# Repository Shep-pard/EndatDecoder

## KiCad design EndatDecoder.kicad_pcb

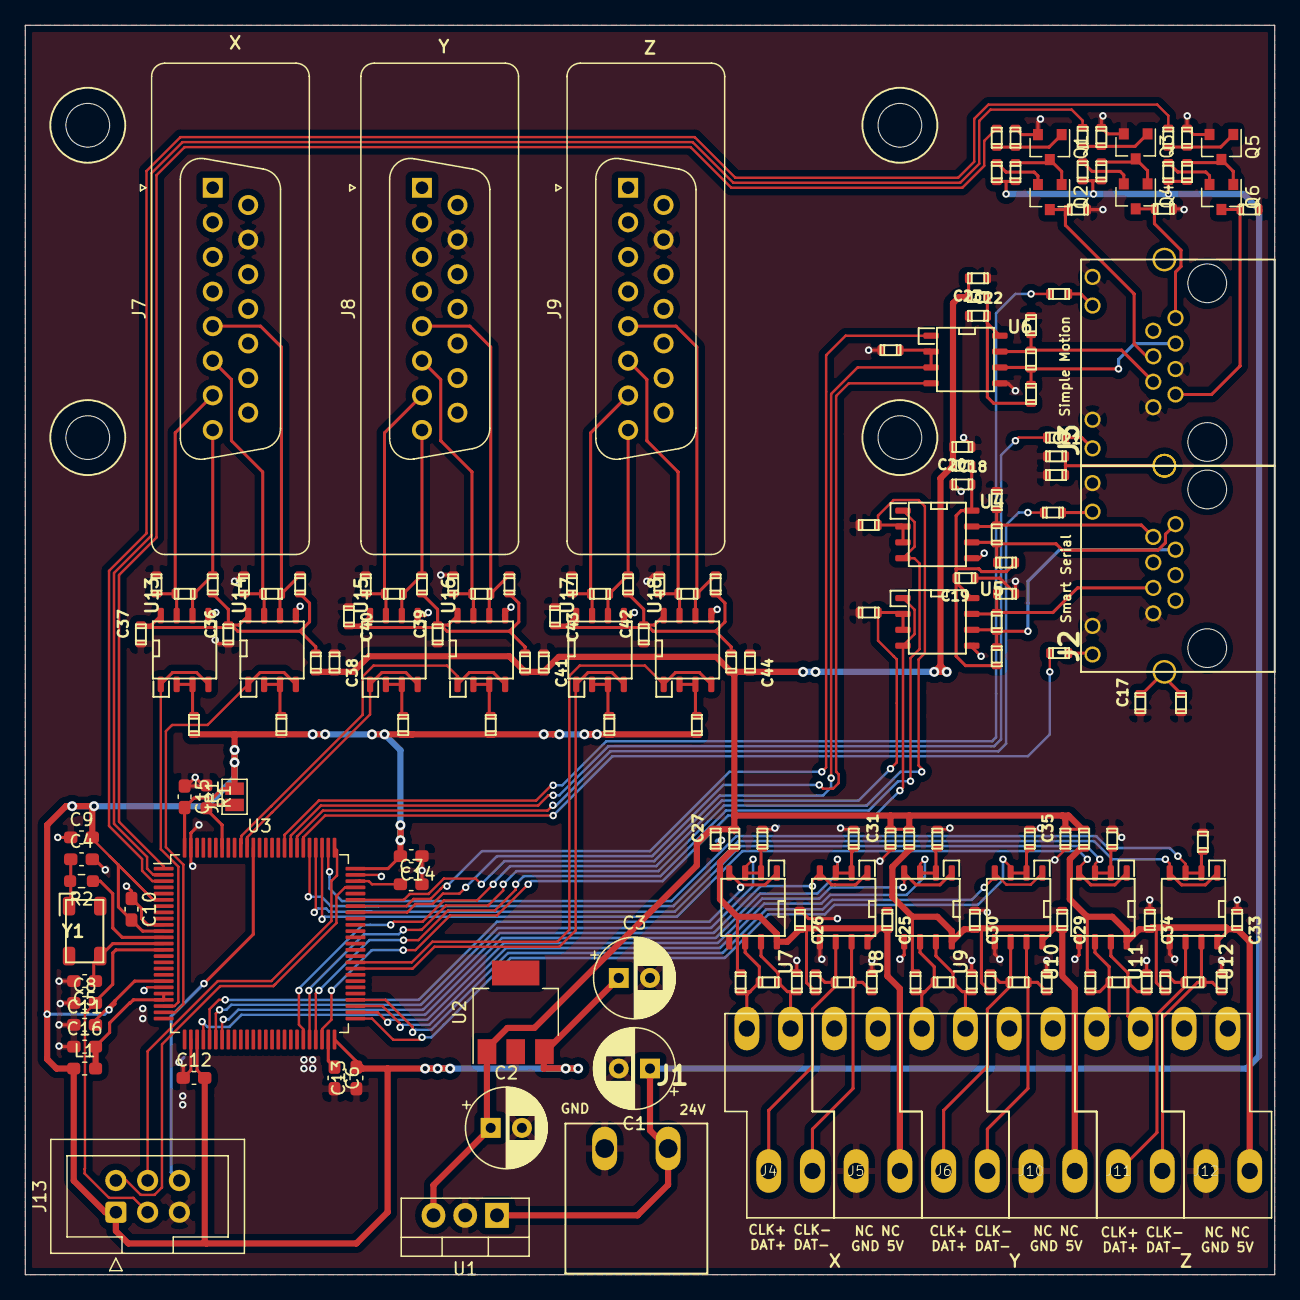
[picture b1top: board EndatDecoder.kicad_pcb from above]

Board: 2 copper layers, 100.0 x 100.0 mm, 176 parts (0 on the bottom side), 108 nets.

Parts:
C1, C2, C3: CP; CP_Radial_D6.3mm_P2.50mm
C4, C5: 18p; C_0603_1608Metric_Pad1.08x0.95mm_HandSolder
C6, C7: 2.2u; C_0603_1608Metric_Pad1.08x0.95mm_HandSolder
C8, C9, C10, C11, C12, C13, C14, C15, C16: 100n; C_0603_1608Metric_Pad1.08x0.95mm_HandSolder
C17, C18, C19, C20, C21, C22, C23, C25, C26, C27, C29, C30, C31, C33, C34, C35, C36, C37, C38, C39, C40, C41, C42, C43, C44: 100n; C_0603
J1: Conn_01x02; RM5.08_1x2
J2, J3: RJ45_LED
J4, J5, J6, J10, J11, J12: Conn_01x04; TERMINAL_BLOCK_2PIN_3.5
J7, J8, J9: DB15_Female; DSUB-15_Female_Vertical_P2.77x2.84mm
J13: Conn_02x03_Odd_Even; IDC-Header_2x03_P2.54mm_Vertical
JP1: Jumper_2_Open; SolderJumper-2_P1.3mm_Open_Pad1.0x1.5mm
L1: 220r 700mA; L_0603_1608Metric_Pad1.05x0.95mm_HandSolder
L2, L3, L4, L5, L6, L7, L8, L9: 220r 700mA; R_0603
Q1, Q3, Q5: AO3400A; SOT-23
Q2, Q4, Q6: AO3401A; SOT-23
R1: R; R_0603_1608Metric_Pad0.98x0.95mm_HandSolder
R2: 0; R_0603_1608Metric_Pad0.98x0.95mm_HandSolder
R3, R12, R32, R33, R34, R43: 120; R_0603
R4, R6, R7, R9, R10, R11, R14, R15, R16, R18, R20, R22, R23, R24, R26, R28, R29, R31, R35, R37, R38, R40, R46, R48, R49, R51, R57, R59, R60, R62, R65, R67, R68, R70, R71, R72, R73, R75, R76, R78, R79, R80, R81, R83, R84, R86, R87, R88: 10k; R_0603
R5, R8, R17, R36, R39, R41, R42, R47, R50, R52, R53, R58, R61, R63, R64, R66, R69, R74, R77, R82, R85: 1k; R_0603
R13, R19, R21, R25, R27, R30: 100; R_0603
U1: LM7805_TO220; TO-220-3_Vertical
U2: L78033; SOT-223
U3: STM32F405VGTx; LQFP-100_14x14mm_P0.5mm
U4, U5, U6, U7, U8, U9, U10, U11, U12, U13, U14, U15, U16, U17, U18: SN65176B; SOIC-8-N
U19, U20, U21, U22: non_plated; non_plated_3mm
Y1: Crystal; Crystal_SMD_0503_4Pads

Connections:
+3.3VA: C16.2, L1.2, U3.21, U3.22
+3V3: C3.1, C9.2, C10.2, C11.2, C12.2, C13.2, C14.2, C15.2, J13.1, JP1.2, L1.1, R71.1, R72.1, R79.1, R80.1, R87.1, R88.1, U2.3, U3.6, U3.11, U3.19, U3.28, U3.50, U3.75, U3.100
+5F: C2.1, C20.1, C23.1, C27.1, C31.1, C35.1, C38.1, C41.1, C44.1, L2.2, L3.2, L4.2, L5.2, L6.2, L7.2, L8.2, L9.2, U1.3, U2.1
+24V: C1.1, J1.1, R15.1, R19.1, R23.1, R25.1, R29.1, R30.1, U1.1
/Endat1/CLK: U3.30, U7.1, U7.4
/Endat1/CLK_EN: R41.1, U3.31, U7.2, U7.3
/Endat1/MOSI: U3.32, U8.1, U8.4
/Endat1/MOSI_EN: R42.1, U3.29, U8.2, U8.3
/Endat2/CLK: U3.52, U9.1, U9.4
/Endat2/CLK_EN: R52.1, U3.53, U9.2, U9.3
/Endat2/MOSI: U3.54, U10.1, U10.4
/Endat2/MOSI_EN: R53.1, U3.51, U10.2, U10.3
/Endat3/CLK: U3.78, U11.1, U11.4
/Endat3/CLK_EN: R63.1, U3.79, U11.2, U11.3
/Endat3/MOSI: U3.80, U12.1, U12.4
/Endat3/MOSI_EN: R64.1, U3.77, U12.2, U12.3
/QuadOut1/A: U3.23, U13.1, U13.4
/QuadOut1/B: U3.24, U14.1, U14.4
/QuadOut1/DIR1: R71.2, U13.2, U13.3
/QuadOut1/DIR2: R72.2, U14.2, U14.3
/QuadOut2/A: U3.90, U15.1, U15.4
/QuadOut2/B: U3.91, U16.1, U16.4
/QuadOut2/DIR1: R79.2, U15.2, U15.3
/QuadOut2/DIR2: R80.2, U16.2, U16.3
/QuadOut3/A: U3.59, U17.1, U17.4
/QuadOut3/B: U3.60, U18.1, U18.4
/QuadOut3/DIR1: R87.2, U17.2, U17.3
/QuadOut3/DIR2: R88.2, U18.2, U18.3
/SimpleMotionV2/DIR: R24.1, U3.70, U6.2, U6.3
/SimpleMotionV2/EN: R27.2, U3.3
/SimpleMotionV2/EN_24: J3.7, Q6.3, R31.1
/SimpleMotionV2/LD1: R34.2, U3.84
/SimpleMotionV2/LD2: R43.2, U3.83
/SimpleMotionV2/RX: U3.69, U6.1
/SimpleMotionV2/STO1: R13.2, U3.1
/SimpleMotionV2/STO1_24: J3.4, Q2.3, R20.1
/SimpleMotionV2/STO2: R21.2, U3.2
/SimpleMotionV2/STO2_24: J3.1, Q4.3, R26.1
/SimpleMotionV2/TX: U3.68, U6.4
/controller/NRST: C8.2, J13.3, U3.14
/controller/SWCLK: J13.4, U3.76
/controller/SWDIO: J13.2, U3.72
/controller/SWO: J13.6, U3.89
/sserial_1/DIR1: R10.1, U3.46, U4.2, U4.3
/sserial_1/DIR2: R11.1, U3.45, U5.2, U5.3
/sserial_1/LD1: R32.2, U3.82
/sserial_1/LD2: R33.2, U3.81
/sserial_1/RX: U3.48, U5.1, U5.4
/sserial_1/TX: U3.47, U4.1, U4.4
GND: C1.2, C2.2, C3.2, C4.2, C5.2, C6.2, C7.2, C8.1, C9.1, C10.1, C11.1, C12.1, C13.1, C14.1, C15.1, C16.1, C17.2, C18.2, C19.2, C20.2, C21.2, C22.2, C23.2, C25.2, C26.2, C27.2, C29.2, C30.2, C31.2, C33.2, C34.2, C35.2, C36.2, C37.2, C38.2, C39.2, C40.2, C41.2, C42.2, C43.2, C44.2, J1.2, J2.8, J2.9, J2.11, J3.5, J3.8, J3.9, J3.11, J5.2, J7.10, J8.10, J9.10, J10.2, J12.2, J13.5, Q1.2, Q3.2, Q5.2, R1.1, R3.2, R6.2, R9.2, R10.2, R11.2, R12.2, R14.2, R18.2, R20.2, R22.2, R24.2, R26.2, R28.2, R31.2, R37.2, R40.2, R41.2, R42.2, R48.2, R51.2, R52.2, R53.2, R59.2, R62.2, R63.2, R64.2, R67.2, R70.2, R75.2, R78.2, R83.2, R86.2, U1.2, U2.2, U3.10, U3.20, U3.27, U3.74, U3.99, U4.5, U5.5, U6.5, U7.5, U8.5, U9.5, U10.5, U11.5, U12.5, U13.5, U14.5, U15.5, U16.5, U17.5, U18.5
GNDD: C17.1, C21.1, J2.13, J3.13, R3.1, R12.1
unnamed: C4.1, R2.2, Y1.1
unnamed: C5.1, U3.13, Y1.2
unnamed: C6.1, U3.49
unnamed: C7.1, U3.73
unnamed: C18.1, C19.1, L2.1, R4.1, R7.1, U4.8, U5.8
unnamed: C22.1, L3.1, R16.1, U6.8
unnamed: C25.1, C26.1, J5.4, L4.1, R35.1, R38.1, U7.8, U8.8
unnamed: C29.1, C30.1, J10.4, L5.1, R46.1, R49.1, U9.8, U10.8
unnamed: C33.1, C34.1, J12.4, L6.1, R57.1, R60.1, U11.8, U12.8
unnamed: C36.1, C37.1, L7.1, R65.1, R68.1, U13.8, U14.8
unnamed: C39.1, C40.1, L8.1, R73.1, R76.1, U15.8, U16.8
unnamed: C42.1, C43.1, L9.1, R81.1, R84.1, U17.8, U18.8
unnamed: J2.1, R4.2, R5.1, U4.6
unnamed: J2.2, R5.2, R6.1, U4.7
unnamed: J2.3, R7.2, R8.1, U5.6
unnamed: J2.6, R8.2, R9.1, U5.7
unnamed: J2.10, R33.1
unnamed: J2.12, R32.1
unnamed: J3.3, R16.2, R17.1, U6.6
unnamed: J3.6, R17.2, R18.1, U6.7
unnamed: J3.10, R43.1
unnamed: J3.12, R34.1
unnamed: J4.1, R35.2, R36.1, U7.6
unnamed: J4.2, R38.2, R39.1, U8.6
unnamed: J4.3, R36.2, R37.1, U7.7
unnamed: J4.4, R39.2, R40.1, U8.7
unnamed: J6.1, R46.2, R47.1, U9.6
unnamed: J6.2, R49.2, R50.1, U10.6
unnamed: J6.3, R47.2, R48.1, U9.7
unnamed: J6.4, R50.2, R51.1, U10.7
unnamed: J7.5, R68.2, R69.1, U14.6
unnamed: J7.6, R69.2, R70.1, U14.7
unnamed: J7.7, R66.2, R67.1, U13.7
unnamed: J7.8, R65.2, R66.1, U13.6
unnamed: J8.5, R76.2, R77.1, U16.6
unnamed: J8.6, R77.2, R78.1, U16.7
unnamed: J8.7, R74.2, R75.1, U15.7
unnamed: J8.8, R73.2, R74.1, U15.6
unnamed: J9.5, R84.2, R85.1, U18.6
unnamed: J9.6, R85.2, R86.1, U18.7
unnamed: J9.7, R82.2, R83.1, U17.7
unnamed: J9.8, R81.2, R82.1, U17.6
unnamed: J11.1, R57.2, R58.1, U11.6
unnamed: J11.2, R60.2, R61.1, U12.6
unnamed: J11.3, R58.2, R59.1, U11.7
unnamed: J11.4, R61.2, R62.1, U12.7
unnamed: JP1.1, R1.2, U3.94
unnamed: Q1.1, R13.1, R14.1
unnamed: Q1.3, Q2.1, R15.2
unnamed: Q2.2, R19.2
unnamed: Q3.1, R21.1, R22.1
unnamed: Q3.3, Q4.1, R23.2
unnamed: Q4.2, R25.2
unnamed: Q5.1, R27.1, R28.1
unnamed: Q5.3, Q6.1, R29.2
unnamed: Q6.2, R30.2
unnamed: R2.1, U3.12

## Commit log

2021-12-14 added sw
2021-12-14 added pdf schematic
2021-12-16 added sysview
2021-12-16 added quadature output
